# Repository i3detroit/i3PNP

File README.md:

i3PNP
=====

Driver boards for the 6-axis autosampler-cum-pick-and-place at i3Detroit.

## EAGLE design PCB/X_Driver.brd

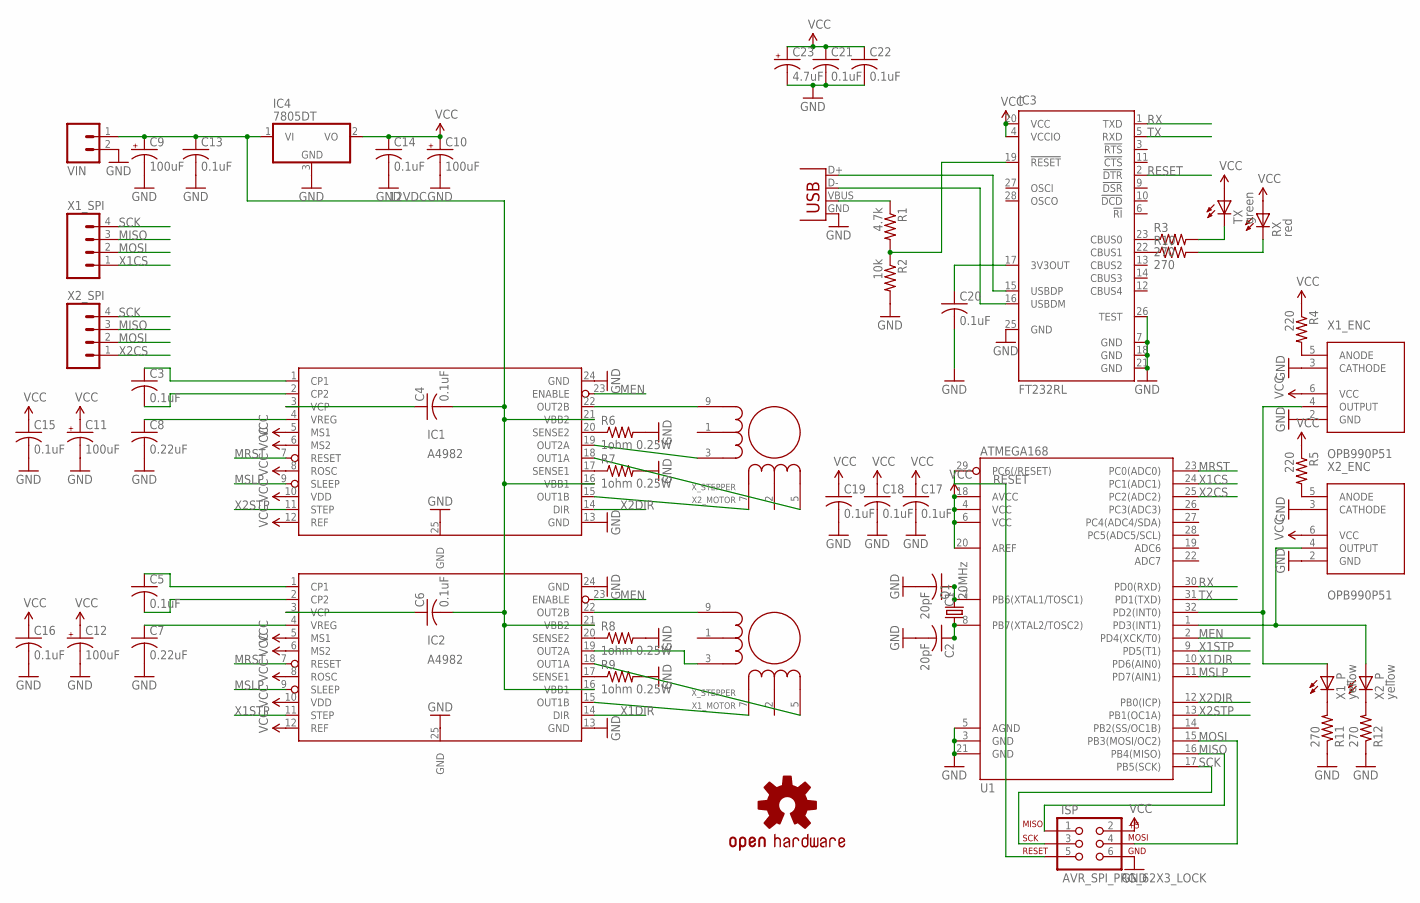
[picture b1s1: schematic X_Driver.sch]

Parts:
C1, C2: 20pF; C0603
C3, C4, C5, C6, C13, C14, C15, C16, C17, C18, C19, C20, C21, C22: 0.1uF; C0603
C7, C8: 0.22uF; C0603
C9, C10, C11, C12: 100uF; 153CLV-0505
C23: 4.7uF; 153CLV-0505
IC1, IC2: A4982; 24TSSOP
IC3: FT232RL; SSOP28
IC4: 7805DT; TO252
ISP: AVR_SPI_PRG_62X3_LOCK; 2X3_LOCK
Q1: 20MHz; HC49UP
R1: 4.7k; R0603
R2: 10k; R0603
R3, R10, R11, R12: 270; R0603
R4, R5: 220; R0603
R6, R7, R8, R9: 1ohm 0.25W; R0603
RX: red; CHIP-LED0603
TX: green; CHIP-LED0603
U1: ATMEGA168; TQFP32-08
U$1: OSHW-LOGOM; OSHW-LOGO-M
VIN: M025MM; SCREWTERMINAL-5MM-2
X1: USBSMD; USB-MINIB
X1_ENC, X2_ENC: OPB990P51
X1_MOTOR, X2_MOTOR: X_STEPPER; 2X5_SHROUDED
X1_P, X2_P: yellow; CHIP-LED0603
X1_SPI, X2_SPI: M04LOCK; 1X04_LOCK

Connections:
12VDC: C4.2, C6.2, C9.+, C13.1, IC1.16 (VBB1), IC1.21 (VBB2), IC2.16 (VBB1), IC2.21 (VBB2), IC4.1 (VI), VIN.1
GND: C1.2, C2.2, C7.2, C8.2, C9.-, C10.-, C11.-, C12.-, C13.2, C14.2, C15.2, C16.2, C17.2, C18.2, C19.2, C20.2, C21.2, C22.2, C23.-, IC1.13 (GND), IC1.24 (GND), IC1.25 (GND), IC2.13 (GND), IC2.24 (GND), IC2.25 (GND), IC3.7 (GND), IC3.18 (GND), IC3.21 (GND), IC3.25 (GND), IC3.26 (TEST), IC4.3 (GND), ISP.6, R2.2, R6.2, R7.2, R8.2, R9.2, R11.1, R12.1, U1.3 (GND), U1.5 (AGND), U1.21 (GND), VIN.2, X1.GND, X1_ENC.2 (GND), X1_ENC.3 (CATHODE), X2_ENC.2 (GND), X2_ENC.3 (CATHODE)
MEN: IC1.23 (ENABLE), IC2.23 (ENABLE), U1.2 (PD4(XCK/T0))
MISO: ISP.1, U1.16 (PB4(MISO)), X1_SPI.3, X2_SPI.3
MOSI: ISP.4, U1.15 (PB3(MOSI/OC2)), X1_SPI.2, X2_SPI.2
MRST: IC1.7 (RESET), IC2.7 (RESET), U1.23 (PC0(ADC0))
MSLP: IC1.9 (SLEEP), IC2.9 (SLEEP), U1.11 (PD7(AIN1))
unnamed: C1.1, Q1.2, U1.7 (PB6(XTAL1/TOSC1))
unnamed: C2.1, Q1.1, U1.8 (PB7(XTAL2/TOSC2))
unnamed: C20.1, IC3.17 (3V3OUT)
unnamed: IC3.19 (!RESET), R1.2, R2.1
unnamed: R1.1, X1.VBUS
unnamed: R4.2, X1_ENC.5 (ANODE)
unnamed: R5.2, X2_ENC.5 (ANODE)
unnamed: IC1.18 (OUT1A), X2_MOTOR.5 (A1)
unnamed: U1.1 (PD3(INT1)), X2_ENC.4 (OUTPUT), X2_P.A
unnamed: U1.32 (PD2(INT0)), X1_ENC.4 (OUTPUT), X1_P.A
unnamed: IC3.16 (USBDM), X1.D-
unnamed: C5.1, IC2.1 (CP1)
unnamed: C5.2, IC2.2 (CP2)
unnamed: C3.1, IC1.1 (CP1)
unnamed: C3.2, IC1.2 (CP2)
unnamed: C4.1, IC1.3 (VCP)
unnamed: IC1.15 (OUT1B), X2_MOTOR.7 (A2)
unnamed: C6.1, IC2.3 (VCP)
unnamed: IC1.19 (OUT2A), X2_MOTOR.3 (B1)
unnamed: C8.1, IC1.4 (VREG)
unnamed: C7.1, IC2.4 (VREG)
unnamed: IC1.22 (OUT2B), X2_MOTOR.9 (B2)
unnamed: IC2.18 (OUT1A), X1_MOTOR.5 (A1)
unnamed: IC2.15 (OUT1B), X1_MOTOR.7 (A2)
unnamed: IC2.22 (OUT2B), X1_MOTOR.9 (B2)
unnamed: IC2.19 (OUT2A), X1_MOTOR.3 (B1)
unnamed: IC3.15 (USBDP), X1.D+
unnamed: IC3.23 (CBUS0), R3.1
unnamed: IC1.20 (SENSE2), R6.1
unnamed: IC1.17 (SENSE1), R7.1
unnamed: IC2.20 (SENSE2), R8.1
unnamed: IC2.17 (SENSE1), R9.1
unnamed: IC3.22 (CBUS1), R10.1
unnamed: R3.2, TX.C
unnamed: R10.2, RX.C
unnamed: R11.2, X1_P.C
unnamed: R12.2, X2_P.C
RESET: IC3.2 (!DTR), ISP.5, U1.29 (PC6(/RESET))
RX: IC3.1 (TXD), U1.30 (PD0(RXD))
SCK: ISP.3, U1.17 (PB5(SCK)), X1_SPI.4, X2_SPI.4
TX: IC3.5 (RXD), U1.31 (PD1(TXD))
VCC: C10.+, C11.+, C12.+, C14.1, C15.1, C16.1, C17.1, C18.1, C19.1, C21.1, C22.1, C23.+, IC1.5 (MS1), IC1.6 (MS2), IC1.8 (ROSC), IC1.10 (VDD), IC1.12 (REF), IC2.5 (MS1), IC2.6 (MS2), IC2.8 (ROSC), IC2.10 (VDD), IC2.12 (REF), IC3.4 (VCCIO), IC3.20 (VCC), IC4.2 (VO), ISP.2, R4.1, R5.1, RX.A, TX.A, U1.4 (VCC), U1.6 (VCC), U1.18 (AVCC), U1.20 (AREF), X1_ENC.6 (VCC), X2_ENC.6 (VCC)
X1CS: U1.24 (PC1(ADC1)), X1_SPI.1
X1DIR: IC2.14 (DIR), U1.10 (PD6(AIN0))
X1STP: IC2.11 (STEP), U1.9 (PD5(T1))
X2CS: U1.25 (PC2(ADC2)), X2_SPI.1
X2DIR: IC1.14 (DIR), U1.12 (PB0(ICP))
X2STP: IC1.11 (STEP), U1.13 (PB1(OC1A))

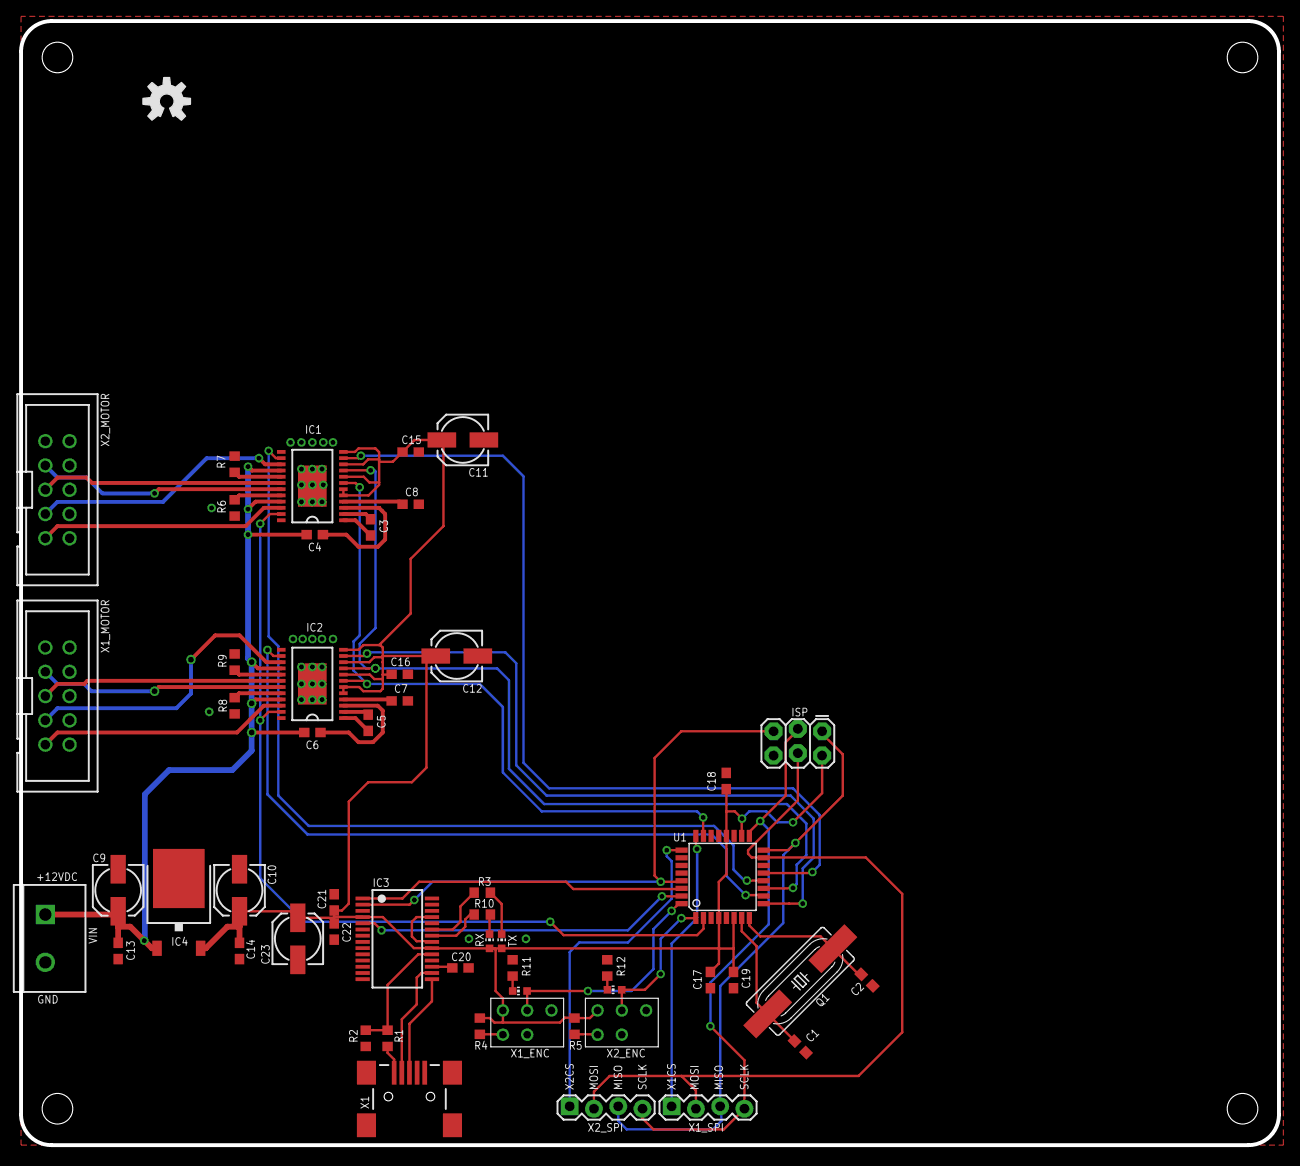
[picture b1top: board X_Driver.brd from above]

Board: 2 copper layers, 131.6 x 117.6 mm, 55 parts (0 on the bottom side), 55 nets.

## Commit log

2013-04-06 Initial commit, Y/Z arm driver is done; X driver still needs layout.
2013-04-06 Added directory structure for future development.
2013-04-06 Removed PCB placeholder
2013-04-06 Added SVG pinouts for connectors.
2013-04-09 Routed X driver, both boards need DRC.
2017-09-04 Leftover changes from decommissioned machine

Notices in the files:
parts and their libraries:
SparkFun: Licensing: CC v3.0 Share-Alike You are welcome to use this library for commercial purposes.
